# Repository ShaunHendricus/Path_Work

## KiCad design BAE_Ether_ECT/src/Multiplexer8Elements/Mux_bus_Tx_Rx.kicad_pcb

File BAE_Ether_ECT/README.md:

# BEA_systems_ECT
 Code and datasheets related to Ether NDE ETi-300

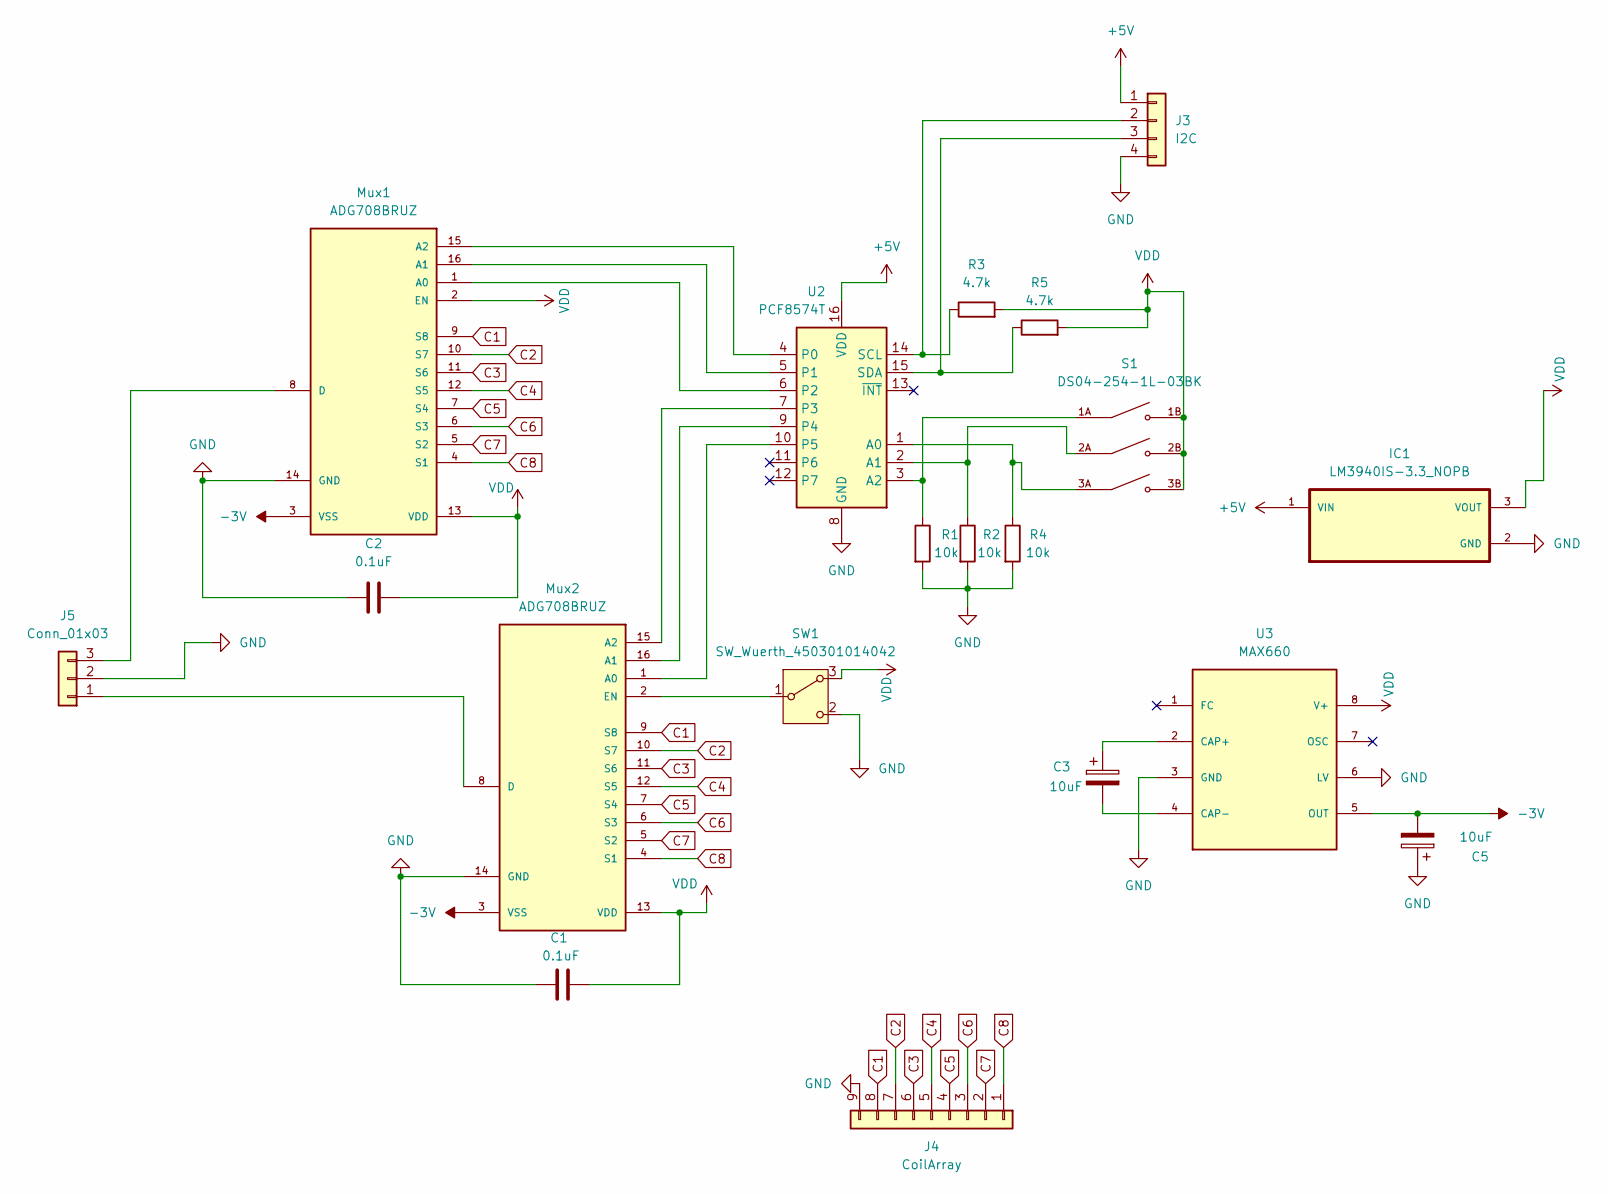
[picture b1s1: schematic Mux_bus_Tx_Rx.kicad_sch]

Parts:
C1, C2: 0.1uF; C_0805_2012Metric_Pad1.18x1.45mm_HandSolder
C3, C5: 10uF; C_Radial_D5.0mm_H11.0mm_P2.00mm
IC1: LM3940IS-3.3_NOPB; SOT230P700X180-4N
J3: I2C; JST_XH_B4B-XH-A_1x04_P2.50mm_Vertical
J4: CoilArray; Molex_200528-0090_1x09-1MP_P1.00mm_Horizontal
J5: Conn_01x03; JST_EH_B3B-EH-A_1x03_P2.50mm_Vertical
Mux1, Mux2: ADG708BRUZ; TSSOP16
R1, R2, R4: 10k; R_0805_2012Metric_Pad1.20x1.40mm_HandSolder
R3, R5: 4.7k; R_0805_2012Metric_Pad1.20x1.40mm_HandSolder
S1: DS04-254-1L-03BK; SW_DS04-254-1L-03BK; PARTREV V0.0
SW1: SW_Wuerth_450301014042; SW_Slide-03_Wuerth-WS-SLTV_10x2.5x6.4_P2.54mm
U2: PCF8574T; SOIC-16W_7.5x10.3mm_P1.27mm
U3: MAX660; SO08

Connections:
+5V: IC1.1 (VIN), J3.1, U2.16 (VDD)
-3V: C5.2, Mux1.3 (VSS), Mux2.3 (VSS), U3.5 (OUT)
C1: J4.8, Mux1.9 (S8), Mux2.9 (S8)
C2: J4.7, Mux1.10 (S7), Mux2.10 (S7)
C3: J4.6, Mux1.11 (S6), Mux2.11 (S6)
C4: J4.5, Mux1.12 (S5), Mux2.12 (S5)
C5: J4.4, Mux1.7 (S4), Mux2.7 (S4)
C6: J4.3, Mux1.6 (S3), Mux2.6 (S3)
C7: J4.2, Mux1.5 (S2), Mux2.5 (S2)
C8: J4.1, Mux1.4 (S1), Mux2.4 (S1)
GND: C1.2, C2.2, C5.1, IC1.2 (GND), J3.4, J4.9, J5.2, Mux1.14 (GND), Mux2.14 (GND), R1.2, R2.2, R4.2, SW1.2 (C), U2.8 (GND), U3.3 (GND), U3.6 (LV)
unnamed: J3.2, R3.1, U2.14 (SCL)
unnamed: J3.3, R5.1, U2.15 (SDA)
unnamed: J5.1, Mux2.8 (D)
unnamed: J5.3, Mux1.8 (D)
unnamed: Mux1.1 (A0), U2.6 (P2)
unnamed: Mux1.16 (A1), U2.5 (P1)
unnamed: Mux1.15 (A2), U2.4 (P0)
unnamed: Mux2.1 (A0), U2.10 (P5)
unnamed: Mux2.16 (A1), U2.9 (P4)
unnamed: Mux2.15 (A2), U2.7 (P3)
unnamed: Mux2.2 (EN), SW1.1 (B)
unnamed: R4.1, S1.3A, U2.1 (A0)
unnamed: R2.1, S1.2A, U2.2 (A1)
unnamed: R1.1, S1.1A, U2.3 (A2)
unnamed: C3.1, U3.2 (CAP+)
unnamed: C3.2, U3.4 (CAP-)
VDD: C1.1, C2.1, IC1.3 (VOUT), Mux1.2 (EN), Mux1.13 (VDD), Mux2.13 (VDD), R3.2, R5.2, S1.1B, S1.2B, S1.3B, SW1.3 (A), U3.8 (V+)

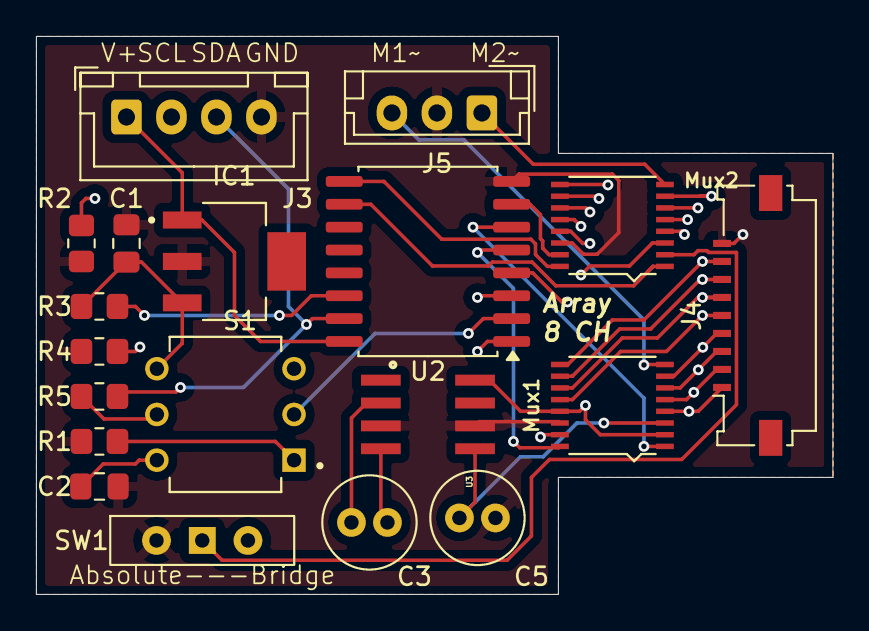
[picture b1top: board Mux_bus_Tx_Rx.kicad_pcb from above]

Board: 4 copper layers, 44.2 x 31.0 mm, 19 parts (0 on the bottom side), 28 nets.
